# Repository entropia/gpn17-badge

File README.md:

# GPN17 Badge
GPN Badge (Gulasch Push Notifications)

HowTo SetUp arduino:
- Install the newest arduino Version (tested with 1.8.2) from the [Arduino website](http://www.arduino.cc/en/main/software).
- Start Arduino and open Preferences window.
- Enter ```https://rawgit.com/entropia/gpn17-badge/master/arduino/package_gpnbadge_index.json``` into *Additional Board Manager URLs* field. You can add multiple URLs, separating them with commas.
- Open Boards Manager from Tools > Board menu and install *gpnbadge* platform (and don't forget to select the GPN Badge board from Tools > Board menu after installation).

To use multirom ability, please add 
```#include "rboot.h"```
to each of your sketches. This replaces the cache function in the libmain.a
Please note: For the moment, rboot is configured as following:

- 4 ROMs / 1MB each
- default boot ROM: 1 
- GPIO boot ROM: 0 (usually the ROM select app)

The GPIO boot is initialised by pulling GPIO16 high at POR. This is the same as pressing the center joystick of the GPN Badge at poweron. Other ROMs can be selected by using the rboot config library.

The patched arduino-esp8266 contains all tools for creating the usual eboot arduino roms, as well as rboot roms.
For this, in addition to esptool also Richard Burtons esptool2 ist downloaded and installed.

Have fun!

## Beschreibung
Teilnehmerbadge mit vielen Funktionen für die GPN 17.

## Grafik-lib
https://github.com/entropia/Adafruit-GFX-Library

## Display-lib
https://github.com/antonxy/TFT_ILI9163C

By default this lib allocates a framebuffer.
If your rom is unstable because of little ram you can disable the framebuffer by commenting out `#define FRAMEBUFFER` in the `TFT_ILI9163C.h` file.
This should especially be done for the default rom.

## Arduino-lib
https://github.com/entropia/gpn17-badge-arduinolib

## UI-lib
https://github.com/entropia/gpn17-badge-ui

## Infrared-lib
https://github.com/markszabo/IRremoteESP8266

## Neopixel-lib
https://github.com/adafruit/Adafruit_NeoPixel

## Notification Server
https://github.com/entropia/gpn17-badge-notification-server

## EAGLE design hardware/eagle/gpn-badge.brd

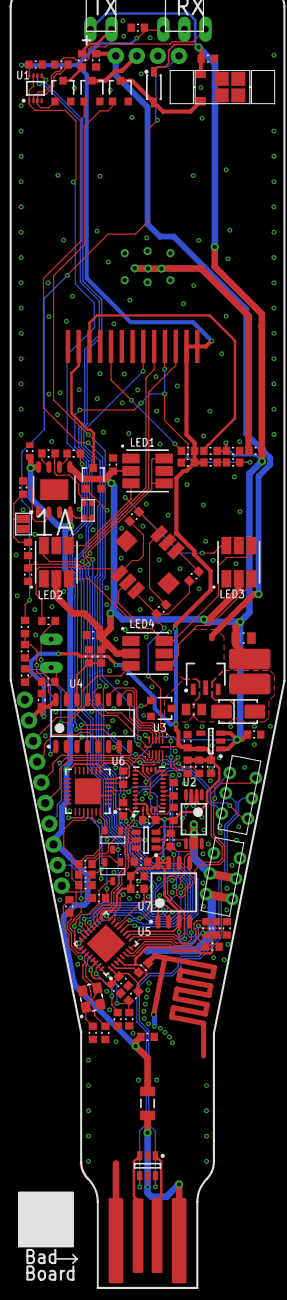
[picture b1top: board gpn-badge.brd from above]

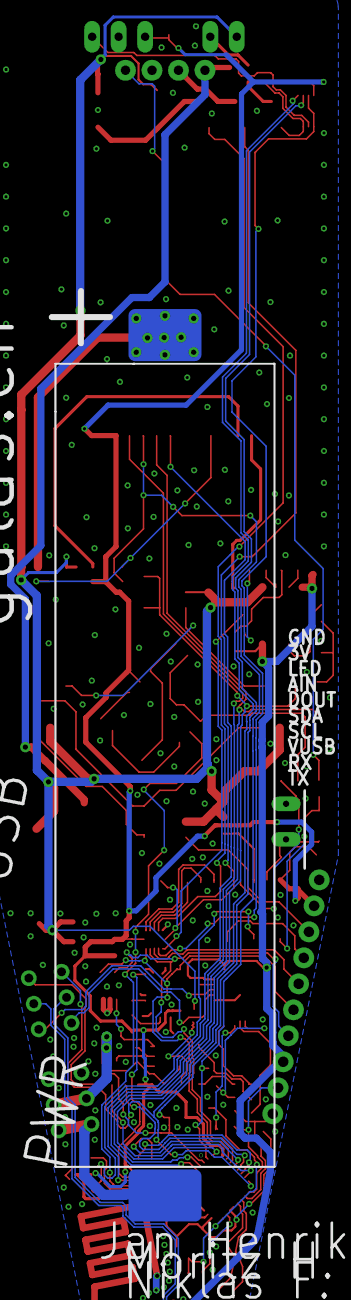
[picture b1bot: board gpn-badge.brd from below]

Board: 2 copper layers, 139 parts (2 on the bottom side), 50 nets.

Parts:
ANT1: ESP-ANTENNA; ESP8266_ANT_1PRIMARY
B1: 18650-Holder; 18650HOLDER-SMD_1PRIMARY
BTN1: joystick; JOYSTICK_1PRIMARY
C1, C3, C6, C9, C18, C32, C34, C35: 100n_25V; C-0603-M_1PRIMARY
C2, C5, C10, C13, C17, C22, C24: 100n_25V; C-0603-M_3PRIMARY
C7: 220p_50V; C-0603-M_3PRIMARY
C14: 5.6p_50V; C-0603-M_5PRIMARY
C15, C19: 5.6p_50V; C-0603-M_1PRIMARY
C16, C23: 1u_10V; C-0603-M_3PRIMARY
C20: 1u_10V; C-0603-M_4PRIMARY
C21: 10u_6,3V; C-0603-M_2PRIMARY
C25: 220p_50V; C-0603-M_1PRIMARY
C26: 10u_6,3V; C-0603-H_1PRIMARY
C27: 10u_6,3V; C-0603-M_3PRIMARY
C29, C36: 1u_10V; C-0603-M_1PRIMARY
C30, C31: 47u_6.3V; C-0805-M_1PRIMARY
D1: BAT54T1G; SOD123_1PRIMARY
D2: B230A-13-F; DIODE-SMA_1PRIMARY
D3: RB520S30T1G; C-0603-M_3PRIMARY
DUMMY1, DUMMY2, DUMMY3, DUMMY18, DUMMY19, DUMMY20, DUMMY21, DUMMY22, DUMMY23, DUMMY24: P:EX79Y79D391
DUMMY4, DUMMY5, DUMMY6, DUMMY7, DUMMY8, DUMMY9, DUMMY10, DUMMY11, DUMMY12, DUMMY13, DUMMY14, DUMMY15: P:EX0Y0D1931
DUMMY16, DUMMY17: P:EX0Y0D2361
DUMMY25, DUMMY26: P:EX0Y0D1381
DUMMY27, DUMMY28: EF59X39TOP1
DUMMY29, DUMMY30: EF51X354TOP1
DUMMY31, DUMMY32: EF70X406TOP1
IC1: TL1838; TL1838_1PRIMARY
IC2: USBLC6-2SC6; SOT23-6_1PRIMARY
IC3: BL8530; SOT89-150P409X160-3N_1PRIMARY
L1: L; L_1PRIMARY
LCD1: LCD; LCD_1PRIMARY
LED1, LED2, LED3, LED4: WS2813; PLCC6_1PRIMARY
LED5: DUO_LED; LEDDUO_1PRIMARY
LED6: IR_LED; IR_LED_1PRIMARY
M1: VIBRATOR; VIBRATOR_SMD_1PRIMARY
P1: Header_4H; HDR1X4H_WO_SILK_1PRIMARY
Q1, Q2, Q5, Q8: AO3400; AO-SOT23-3_V_1PRIMARY
Q3, Q4: NPN_MMBT3904; SOT23-3_1PRIMARY
Q6: AO3400; AO-SOT23-3_V_2PRIMARY
Q7: CEG8205; SOP64P640X265-8N_1PRIMARY
R1, R6, R8: 100k; R-0603-M_1PRIMARY
R2, R27: 100; R-0603-M_2PRIMARY
R3, R10, R11, R15, R16, R19, R23, R24, R25: 12k; R-0603-M_1PRIMARY
R4: 33; R-0603-M_2PRIMARY
R5: 100k; R-0603-M_4PRIMARY
R7: 200k; R-0603-M_1PRIMARY
R9: 100k; R-0603-M_2PRIMARY
R12, R14: 330k; R-0603-M_1PRIMARY
R13: LDR; LDR-5MM_1PRIMARY
R17: 470; R-0603-M_3PRIMARY
R18, R35, R36: 470; R-0603-M_1PRIMARY
R20, R28, R29: 1.2k; R-0603-M_2PRIMARY
R21: 4k7; R-0603-M_1PRIMARY
R22: 12k; R-0603-M_2PRIMARY
R26, R32: 4k7; R-0603-M_2PRIMARY
R30: 1.2k; R-0603-M_1PRIMARY
R31: 0.27; R-1206-M_1PRIMARY
R33, R37: 1M; R-0603-M_2PRIMARY
R34: 0; R-0603-M_1PRIMARY
SW1, SW2: SWITCH_2P2T; SWITCH_THT_1PRIMARY
U1: 74LVC2G125; DCU0008A_L_1PRIMARY
U2: BNO-055_I2C; BNO-055_1PRIMARY
U3: PCA9571; SON40P210X100-10N_1PRIMARY
U4: CD4051BM; D0016A_M_1PRIMARY
U5: ESP8266EX; QFN32-5X5MM_1PRIMARY
U6: CP2102-GM; SLAB-QFN-28-3125X3125TP_M_1PRIMARY
U7: W25Q64; SOIC127P790X100-8N_1PRIMARY
U8: TP4056; SOIC127P600X20_HS-9N_1PRIMARY
U9: DW01A; SOT23-6_1PRIMARY
U10: MIC5501-3.3V; SOT23-5_1PRIMARY
Y1: 26MHz; 3225_1PRIMARY

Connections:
ADC: C7.1, R8.2, U4.3
ALKSNS: R14.1, R37.2, U4.1
BATLVL: R12.1, R33.2, U4.14
ESP_TX: R18.2, R22.2
GND: ANT1.2, IC1.2
IR_EN: U1.1, U1.7, U3.8
JOYSTK: R7.1, U4.13
LCD_LED: Q2.1, U3.7
LCD_RES: C6.2, LCD1.9, R3.2
MQ3_EN: Q6.1, Q8.1, U3.6
NETANT1_1: ANT1.1, C14.2
NETB1_2: SW1.3, SW1.4
NETC10_2: C10.2, U2.9
NETC15_2: C15.2, Y1.1
NETC19_2: C19.2, Y1.3
NETC31_1: C31.1, IC3.1, Q6.3
NETD1_1: D1.1, M1.2, Q1.3
NETD2_1: D2.1, IC3.3, L1.2
NETD3_1: D3.1, R27.1, U9.5
NETD3_2: D3.2, Q7.6, Q7.7, R30.1, SW1.2, SW1.5, U9.6
NETIC1_3: IC1.3, U1.2
NETJ2_1: R28.1, R29.2
NETLCD1_11: LCD1.11, R4.1
NETLCD1_12: LCD1.12, Q2.3
NETLED5_2: LED5.2, R35.2
NETLED5_4: LED5.4, R36.2
NETLED6_2: LED6.2, R2.1
NETQ3_1: Q3.2, R15.2
NETQ4_1: Q4.2, R16.2
NETQ5_1: Q5.1, R10.2, U1.3
NETQ5_3: Q5.3, R2.2
NETQ7_4: Q7.4, U9.3
NETQ7_5: Q7.5, U9.1
NETR11_1: R11.1, U2.4
NETR28_2: R28.2, U8.2
NETR30_2: R30.2, U9.2
NETR35_1: R35.1, U8.7
NETR36_1: R36.1, U8.6
NETU3_1: U3.1, U4.11
NETU3_2: U3.2, U4.10
NETU3_3: U3.3, U4.9
NRST: C25.2, Q3.4, R24.2
SW_N: IC2.6, SW2.2
SW_P: IC2.4, SW2.5
USB_N: R20.1, SW2.3, U1.6
USB_P: SW2.4, U1.5
VBAT: D1.2, LED6.1, M1.1
VBUS: LED5.1, LED5.3, U8.4, U8.8
VIBRATOR: Q1.1, U3.4
VUSB: IC2.5, R31.1

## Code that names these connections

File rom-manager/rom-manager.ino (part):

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#define MUX_ALK 4
#define MUX_IN1 5

#define VIBRATOR 3
#define MQ3_EN   4
#define LCD_LED  5
#define IR_EN    6
#define OUT1     7

#define UP      807
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  Serial.println(ESP.getFlashChipSize());


  setGPIO(LCD_LED, HIGH);

  tft.setFont(&FreeSans9pt7b);
  tft.setTextColor(YELLOW);
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
      if (romNumber == 1) {
        if (digitalRead(16) == HIGH) {
          setGPIO(VIBRATOR, HIGH);
        }
        while (digitalRead(16) == HIGH) {
          delay(10);
        }
        setGPIO(VIBRATOR, LOW);
        stillPressed = true;
      }

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
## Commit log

2017-01-10 ADD: first design files for to badge
2017-01-18 ADD: 3D models, fabrication output for first prototype
2017-02-16 ADD: blank example project for Badge V1.0
2017-02-16 UPD: fixed display orientation
2017-02-19 Pixelflut added
2017-02-26 Added CAD-Files and the alkohol-sensor-sketch
2017-03-04 Fixed sketch for use with the badge
2017-03-05 moved CAD files
2017-03-05 fixed some code
2017-03-05 moved some files
2017-03-19 ADD: rev 2.0 hardware designs
2017-03-22 refined scad model
2017-03-23 UPD: design files for rev. 2.0
2017-04-14 ADD: rboot bootloader support
2017-04-17 ADD: final design drawings
2017-04-21 ADD: gerber files
2017-04-22 ADD: framebuffer example
2017-04-30 ADD: pnp file
2017-04-30 UPD: reverse polarity protection
2017-05-02 INIT: default rom data
2017-05-03 UPD: own, efficient web server
2017-05-04 ADD: GPN-Badge compatible arduino toolchain
2017-05-04 ADD: precompiled rboot
2017-05-04 UPD: bootloader
2017-05-04 DEL: unnecessary large 3D file
2017-05-04 ADD: pre-weakened libmain.a. Also I added the rboot-bigflash to the esp core.
2017-05-04 UPD: patches bootloader for GPIO boot
2017-05-04 UPD: recompile rboot for DIO SPI
2017-05-04 UPD: different memorymap, now with 6x 512kB slots and 1M SPIFFS. Also added rboot-api support to the arduino toolchain
2017-05-10 ADD: experimental eagle version
2017-05-10 ADD: final altium design
2017-05-11 fixed sketch for Badge V2.0
2017-05-11 fixed a calculation
2017-05-11 fixed for version 2
2017-05-11 added comment
2017-05-11 added LDR example
2017-05-11 renamed sketches
2017-05-16 ADD: wifi scan in webinterface
2017-05-16 UPD: -trim get header -less brighter pixels
2017-05-16 DEL: fonts and code link
2017-05-16 More cleanup
2017-05-16 Cleanup
2017-05-16 FIX: correct enumeration of networks
2017-05-16 FIX: use dynamic json buffer
2017-05-16 ADD: mock server for the badge for easier web dev
2017-05-16 UPD: only commit uncompressed files + advanced scan (status, encTypes, signal strength)
2017-05-16 FIX: only allocate download buffer once
2017-05-16 ADD: id of scanned network
2017-05-16 ADD: mock: connect check
2017-05-16 ADD: connect form with API interaction
2017-05-16 ADD: prepare script for compressed data and restructured tree
2017-05-16 FIX: correct static path for mock server
2017-05-16 ADD: small script to prepare data for upload
2017-05-16 ADD: client write timeout
2017-05-16 ADD: cache control header
2017-05-16 FIX: empty net-list before scan
2017-05-16 FIX: some ui glitches + add ui lock
2017-05-16 DEL: old data folder
2017-05-16 UPD: get rid of the arduinoJson lib
2017-05-16 UPD: delete old data before creating new
2017-05-16 DEL: VERSION macro
2017-05-16 ADD: new api + mock for wifi status
2017-05-16 ADD: body parsing
2017-05-16 UPD: new save-api, simulate nick-save
2017-05-16 ADD: nick config
2017-05-16 UPD: impleemmeted new api path for wifi scan
2017-05-16 ADD: wifi status display
2017-05-16 UPD: .h -> .hpp
2017-05-16 ADD: switch between pw and ssid display on joystick interaction
2017-05-16 fixed memory management in url decoder
2017-05-16 add url encoding decoder
2017-05-16 ADD: status api + minor performance improvements
2017-05-16 FIX: don't poll the status while locked
2017-05-16 UPD: filter unsupported enc types
2017-05-16 ADD: implemeted wifi status polling in the webinterface
2017-05-16 ADD: debug output for heap analysis ADD: connect api function (not fully working) UPD: Use rboot UPD: use printf for json generation
2017-05-16 FIX: turn off leds after connect
2017-05-16 ADD: url encoder/writer
2017-05-16 UPD: value is ssid, not id
2017-05-16 FIX: diplay correct number of found networks FIX: wrong behavior on password field
2017-05-16 ADD: write wifi config, read ist and connect! yippie!
2017-05-16 ADD: display connection status
2017-05-17 ADD: connect timeout with wizard access
2017-05-17 ADD: store nickname ADD: 404 for post
2017-05-17 Read channel urls
2017-05-17 WIP: Pull connection
2017-05-18 Verify fingerprint
2017-05-18 Store information fetched from server
2017-05-18 Move notification data handling into new file
2017-05-18 Sync states file with data file
2017-05-18 UPD: use new JoydtickState-Type
2017-05-19 NotificationIterator
2017-05-19 update notification state
2017-05-19 ADD: main menu
2017-05-19 Notification parsing
2017-05-19 vim magic lines
2017-05-19 ADD: menu for stats + start config mode
2017-05-19 UPD: new ui version with ui input dispatch
2017-05-19 ADD: diplay a list of all notifications
2017-05-19 NotificationIterator::setCurrentNotificationState
2017-05-19 New default channel urls
2017-05-19 Only update state if different
2017-05-19 FIX: correct file mode for status update
2017-05-19 ADD: "push" notificate \o/
2017-05-19 notification handle
2017-05-19 ADD: notification display from menu
2017-05-19 FIX: forgot return
2017-05-19 UPD: only active notifications in notification menu
2017-05-19 FIX: disconnect wifi before initialConfig
2017-05-19 api list channels
2017-05-19 Channels web ui
2017-05-19 ADD: env-light dependent theme switch
2017-05-20 CLN: WTF ARDUINO IDE??!
2017-05-20 UPD: #define pull interval and shorten it in #debug mode
2017-05-20 ADD: rudimentary info menu
2017-05-20 ADD: batVoltage to info menu
2017-05-20 ADD: about page
2017-05-20 UPD: use more screenspace for the info menu
2017-05-21 ADD: Feed overlay with data
2017-05-21 ADD: ROM manager
2017-05-21 UPD: make badge usable even if teher is no wifi
2017-05-21 UPD: rboot support for 8MB Flash
2017-05-21 UPD: HttpUpdate now supports updates to specific address
2017-05-21 FIX: let the leds some time before they are turned off
2017-05-21 UPD: more understandable Flash Slot description
2017-05-21 ADD: display if polling in status bar
2017-05-21 UPD: stronger averaging for battery value
2017-05-21 ADD: display unit for RSSI
2017-05-22 Add/Delete channels from webinterface
2017-05-22 url: decode '+' to ' '
2017-05-22 web: channels: validity checks
2017-05-22 check if timestamps exist before recalculating states
2017-05-22 ADD: no busy wait
2017-05-22 FIXED: includes
2017-05-22 refactored webserver
2017-05-23 Hand Stream into post handlers instead of String
2017-05-23 check write result in static server
2017-05-23 WIP: upload works, but boundary is included at end of file
2017-05-23 upload might work now
2017-05-23 Better debug output
2017-05-23 ADD: getter for theme
2017-05-23 ADD: ultrabodgy config management + theme configuration
2017-05-23 FIX: consistent display
2017-05-23 UPD: define deault theme + consistent filr naming
2017-05-23 check for nullptrs in web handlers
2017-05-23 Badge upload works
2017-05-23 Write rom description at start
2017-05-23 badge display
2017-05-23 remove initial sync flag
2017-05-23 FIX: correct config save/default create check
2017-05-23 UPD: delted factory rest menu entry
2017-05-24 read name from channels
2017-05-24 wifi light
2017-05-24 Use GitHub releases for esptool2, add osx binary for esptool2.
2017-05-24 Channel sharing
2017-05-24 Share: send more often, led
2017-05-24 change spiffs paths to something unique
2017-05-24 change wifi light intensity
2017-05-24 UPD: prefixed config
2017-05-25 UPD: use GPN-IoT
2017-05-25 generate password only once
2017-05-25 Default channels
2017-05-25 remove superverbose debug
2017-05-25 FIX: Merge houps
2017-05-25 allow disabling notifications
2017-05-25 make more responsive during recalc
2017-05-25 Added sensor rom
2017-05-25 added examples
2017-05-25 removed sketches
2017-05-25 use correct tft lib (patched with writeRow)
2017-05-25 Readme: Framebuffer define
2017-05-26 Fix vibration notification
2017-05-26 wifi light fading
2017-05-26 remove poll delay
2017-05-26 pushed to V2.0
2017-05-26 UPD: more stable https update
2017-05-26 Update package_gpnbadge_index.json
    updated dependencies for windows release of esptool2
2017-05-26 gpnbadge package does not pretend to be an update for standard esp8266 repo any more; updated zip to 2.4.0 version from https://public.electronics.fail/
2017-05-26 Change Arduino url to repo
2017-05-26 Change zip url to github
2017-05-26 Really fix the board ZIP URL now ;-)
2017-05-26 add menu item to refresh notifications
2017-05-26 pull notifications at the end of setup ...instead of at the beginning, where WiFi is usually not ready
2017-05-26 wait five seconds for wifi connection at startup this allows us to immediately pull notifications
2017-05-26 add support for other ports than 443
2017-05-26 add clock display
2017-05-27 fixed typo in readme and removed legacy example
2017-06-01 ADD: Binaries for factory reset
2017-07-17 Added esptool2 linux32 release
2019-01-08 Remove version pinning from requirements
